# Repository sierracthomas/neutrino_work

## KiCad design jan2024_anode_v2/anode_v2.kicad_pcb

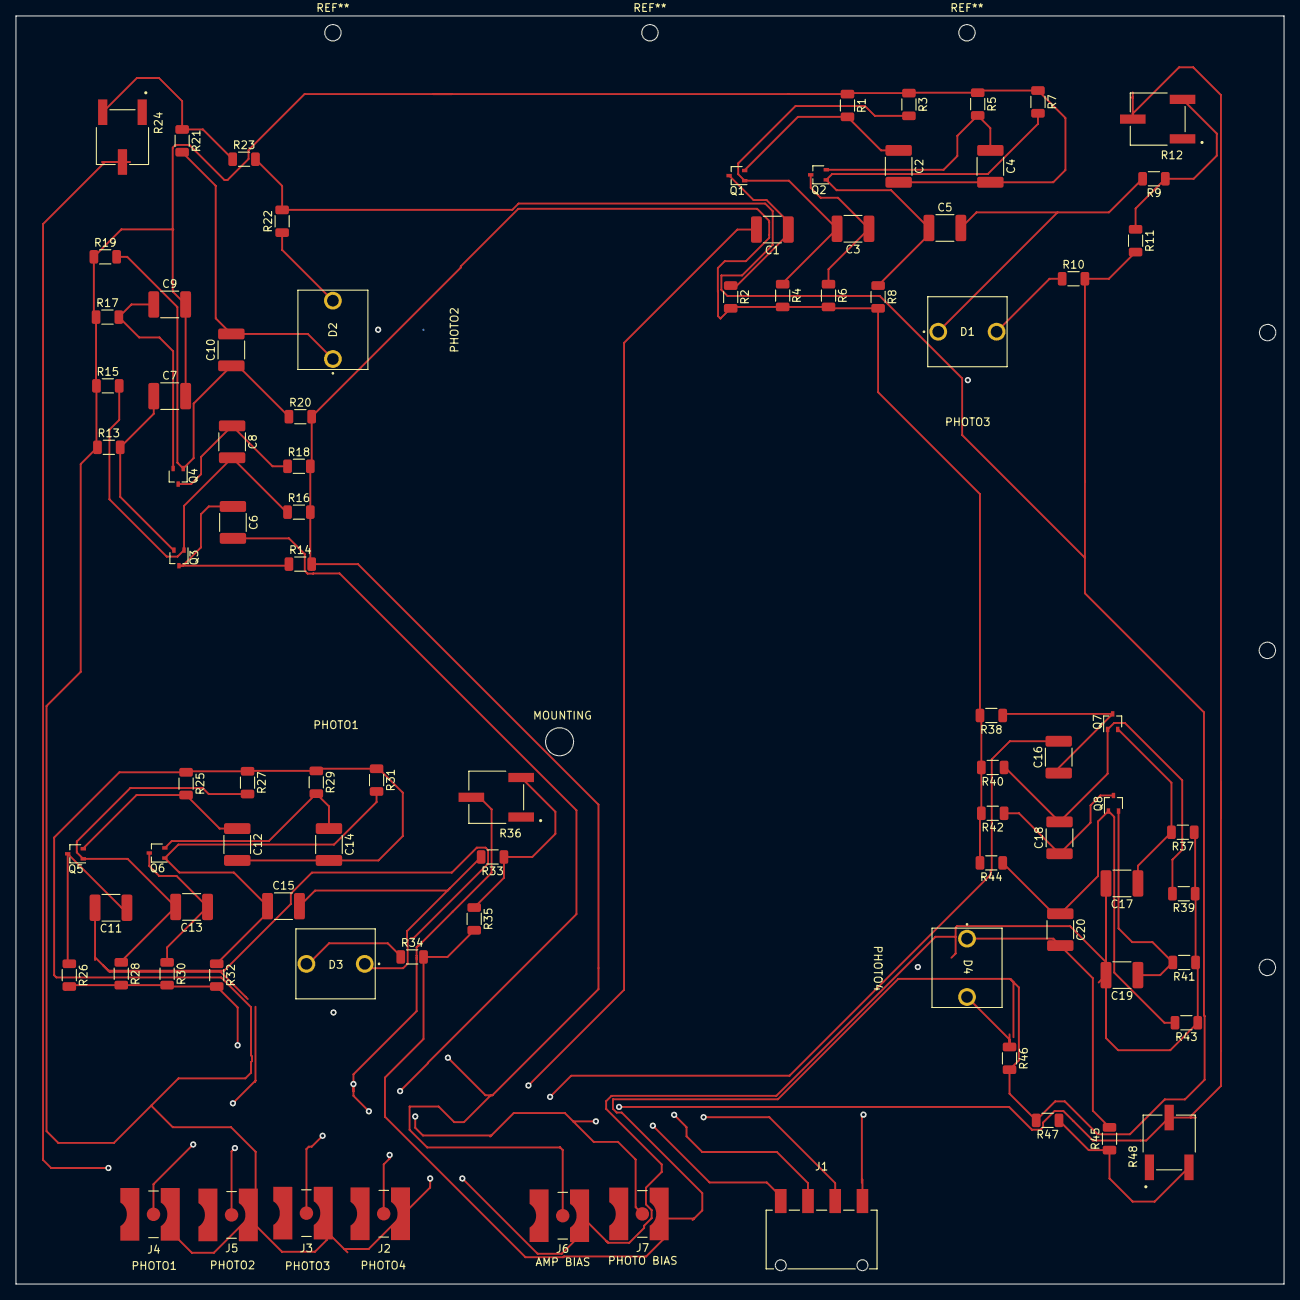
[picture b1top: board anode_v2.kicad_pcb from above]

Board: 4 copper layers, 163.0 x 163.0 mm, 88 parts (0 on the bottom side), 44 nets.

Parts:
C1, C2, C3, C4, C5, C6, C7, C8, C9, C10, C11, C12, C13, C14, C15, C16, C17, C18, C19, C20: C; C_1812_4532Metric
D1: PHOTO3; S13370-6075CN
D2: PHOTO2; S13370-6075CN
D3: PHOTO1; S13370-6075CN
D4: PHOTO4; S13370-6075CN
J1: 430450419; CONN4_2383942-4_TEC
J2: PHOTO4; LINX_CONMCX002-SMD
J3: PHOTO3; LINX_CONMCX002-SMD
J4: PHOTO1; LINX_CONMCX002-SMD
J5: PHOTO2; LINX_CONMCX002-SMD
J6: AMP BIAS; LINX_CONMCX002-SMD
J7: PHOTO BIAS; LINX_CONMCX002-SMD
MOUNTING: MountingHole_2.1mm
Q1, Q2, Q3, Q4, Q5, Q6, Q7, Q8: 2N3904; SOT-323_SC-70
R1, R2, R3, R4, R5, R6, R7, R8, R9, R10, R11, R13, R14, R15, R16, R17, R18, R19, R20, R21, R22, R23, R25, R26, R27, R28, R29, R30, R31, R32, R33, R34, R35, R37, R38, R39, R40, R41, R42, R43, R44, R45, R46, R47: R_US; R_1206_3216Metric
R12, R24, R36, R48: R_Variable_US; TRIM_3361P-1-104GLF

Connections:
/vuv sipm1/SIGNAL: C1.2, J3.1
/vuv sipm2/SIGNAL: C6.2, J5.1
/vuv sipm3/SIGNAL: C11.2, J4.1
/vuv sipm/SIGNAL: C16.2, J2.1
AMP_BIAS: J6.1, R2.2, R4.2, R6.2, R8.2, R14.2, R16.2, R18.2, R20.2, R26.2, R28.2, R30.2, R32.2, R38.2, R40.2, R42.2, R44.2
AMP_GND: C2.2, C4.2, C7.2, C9.2, C12.2, C14.2, C17.2, C19.2, J2.S1, J3.S1, J4.S1, J5.S1, J6.S1, R1.1, R3.1, R5.1, R7.1, R13.1, R15.1, R17.1, R19.1, R25.1, R27.1, R29.1, R31.1, R37.1, R39.1, R41.1, R43.1
BIAS: J7.1, R12.2, R24.2, R36.2, R48.2
GND: J7.S1, R10.2, R11.2, R22.2, R23.2, R34.2, R35.2, R46.2, R47.2
unnamed: C1.1, Q1.3 (C), R2.1
unnamed: C2.1, Q1.2 (E), R1.2
unnamed: C3.1, Q2.3 (C), R6.1
unnamed: C3.2, Q1.1 (B), R3.2, R4.1
unnamed: C5.1, Q2.1 (B), R7.2, R8.1
unnamed: C5.2, D1.1 (K), R9.2
unnamed: C6.1, Q3.3 (C), R14.1
unnamed: C7.1, Q3.2 (E), R13.2
unnamed: C8.1, Q4.3 (C), R18.1
unnamed: C8.2, Q3.1 (B), R15.2, R16.1
unnamed: C10.1, Q4.1 (B), R19.2, R20.1
unnamed: C10.2, D2.1 (K), R21.2
unnamed: C11.1, Q5.3 (C), R26.1
unnamed: C12.1, Q5.2 (E), R25.2
unnamed: C13.1, Q6.3 (C), R30.1
unnamed: C13.2, Q5.1 (B), R27.2, R28.1
unnamed: C15.1, Q6.1 (B), R31.2, R32.1
unnamed: C15.2, D3.1 (K), R33.2
unnamed: C17.1, Q7.2 (E), R37.2
unnamed: C18.1, Q8.3 (C), R42.1
unnamed: C20.1, Q8.1 (B), R43.2, R44.1
unnamed: C20.2, D4.1 (K), R45.2
unnamed: D1.2 (A), R10.1
unnamed: D2.2 (A), R22.1
unnamed: D3.2 (A), R34.1
unnamed: D4.2 (A), R46.1
unnamed: C4.1, Q2.2 (E), R5.2
unnamed: C9.1, Q4.2 (E), R17.2
unnamed: C14.1, Q6.2 (E), R29.2
unnamed: C19.1, Q8.2 (E), R41.2
unnamed: R9.1, R11.1, R12.3
unnamed: R21.1, R23.1, R24.3
unnamed: R33.1, R35.1, R36.3
unnamed: C16.1, Q7.3 (C), R38.1
unnamed: C18.2, Q7.1 (B), R39.2, R40.1
unnamed: R45.1, R47.1, R48.3

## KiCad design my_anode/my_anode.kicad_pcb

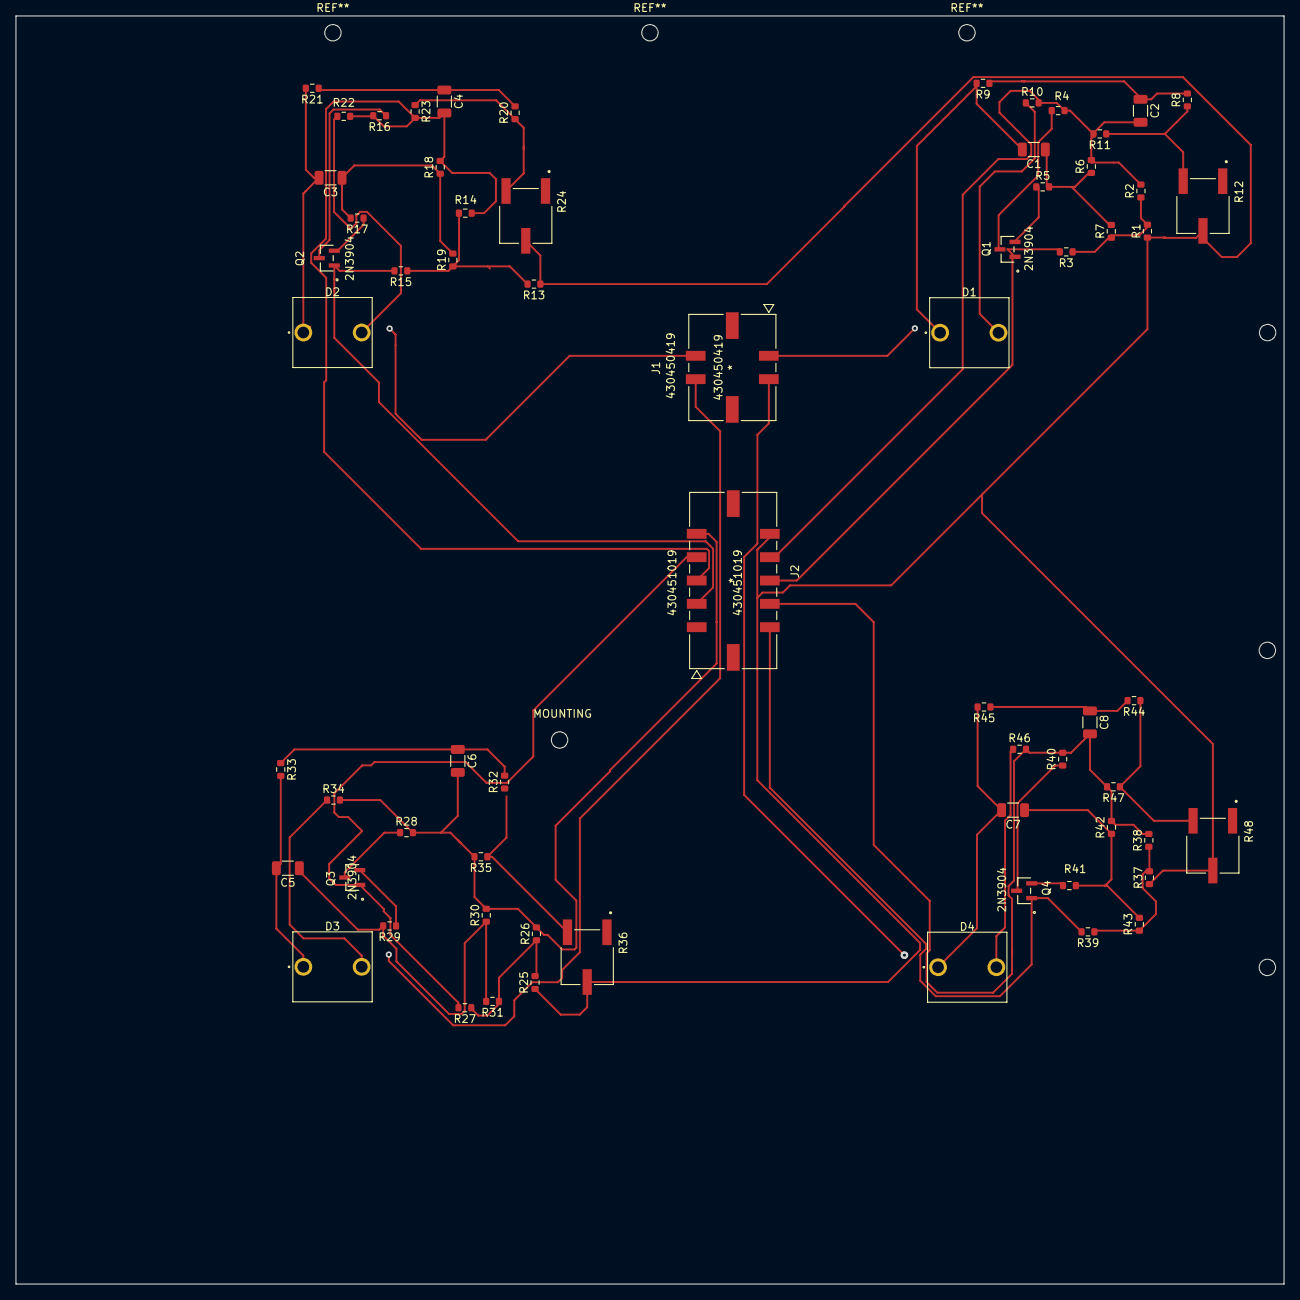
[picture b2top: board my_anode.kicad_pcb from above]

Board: 2 copper layers, 163.0 x 163.0 mm, 67 parts (0 on the bottom side), 41 nets.

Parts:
C1, C2, C3, C4, C5, C6, C7, C8: C; C_1206_3216Metric
D1, D2, D3, D4: D_Photo; S13370-6075CN
J1: 430450419
J2: 430451019
MOUNTING: MountingHole_2.1mm
Q1, Q2, Q3, Q4: 2N3904; BC846BLT3G
R1, R2, R3, R4, R5, R6, R7, R8, R9, R10, R11, R13, R14, R15, R16, R17, R18, R19, R20, R21, R22, R23, R25, R26, R27, R28, R29, R30, R31, R32, R33, R34, R35, R37, R38, R39, R40, R41, R42, R43, R44, R45, R46, R47: R_US; R_0603_1608Metric
R12, R24, R36, R48: R_Variable_US; TRIM_3361P-1-104GLF

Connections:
/B1: J2.10, R1.1, R12.2, R13.1, R24.2, R25.1, R36.2, R37.1, R48.2
/G1: C4.2, J2.3, R14.2, R16.2, R18.2, R22.2, R23.2
/G2: C6.2, J2.5, R26.2, R28.2, R30.2, R34.2, R35.2
/G3: C8.2, J2.7, R38.2, R40.2, R42.2, R46.2, R47.2
/G4: C2.2, J2.9, R2.2, R4.2, R6.2, R10.2, R11.2
/S1: J2.2, Q2.1 (E), R15.2
/S2: J2.4, Q3.1 (E), R27.2
/S3: J2.6, Q4.1 (E), R39.2
/S4: J2.8, Q1.1 (E), R3.2
unnamed: C1.1, R5.2, R6.1, R7.2
unnamed: C1.2, D1.1 (K), R9.2
unnamed: C2.1, R8.2, R9.1
unnamed: C3.1, R17.2, R18.1, R19.2
unnamed: C3.2, D2.1 (K), R21.2
unnamed: C4.1, R20.2, R21.1
unnamed: C5.1, R29.2, R30.1, R31.2
unnamed: C5.2, D3.1 (K), R33.2
unnamed: C6.1, R32.2, R33.1
unnamed: C7.1, R41.2, R42.1, R43.2
unnamed: C7.2, D4.1 (K), R45.2
unnamed: C8.1, R44.2, R45.1
unnamed: D1.2 (A), R10.1
unnamed: D2.2 (A), R22.1
unnamed: D3.2 (A), R34.1
unnamed: D4.2 (A), R46.1
unnamed: Q1.2 (B), R5.1
unnamed: Q1.3 (C), R4.1
unnamed: Q2.2 (B), R17.1
unnamed: Q2.3 (C), R16.1
unnamed: Q3.2 (B), R29.1
unnamed: Q3.3 (C), R28.1
unnamed: Q4.2 (B), R41.1
unnamed: Q4.3 (C), R40.1
unnamed: R1.2, R2.1, R3.1, R7.1
unnamed: R8.1, R11.1, R12.3
unnamed: R13.2, R14.1, R15.1, R19.1
unnamed: R20.1, R23.1, R24.3
unnamed: R25.2, R26.1, R27.1, R31.1
unnamed: R32.1, R35.1, R36.3
unnamed: R37.2, R38.1, R39.1, R43.1
unnamed: R44.1, R47.1, R48.3

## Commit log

2022-12-13 initial files and structure
2022-12-13 add fornax data
2022-12-13 Plots with binning
2022-12-14 add binned interaction plots
2022-12-14 add model data and updated scripts
2022-12-15 plot final touches
2023-01-05 Add more documentation
2023-01-05 add README
2023-01-05 README updates
2023-01-05 clear some chaos
2023-01-31 Update fluence to work with 2d plots
2023-02-03 Add anode project
2023-02-17 set times to be the same, fix `vmin` and `vmax`
2023-02-17 Update anode work with mounting holes
2023-02-26 Add quarter-anode board
2023-03-17 Semi-final board version without voltage divider
2023-03-24 add photodiode dark current data
2023-05-01 Add prelim compton scatter example w/ geant script
2023-05-01 V1 with voltage divider
2023-05-02 Trial w/ 20 hits - graph coincident compton scatters
2023-05-04 Add functions to plot integrated electron energy
2023-05-10 Add anode prior to copying
2023-05-15 Add spectrum energy level runs
2023-05-17 New script gets process files
2023-05-17 Subtract all combinations of tracks in pd.dataframe
2023-05-17 Get unique tracks for event 0 that are > 10mm away
2023-05-17 Ignore performance warnings
2023-05-18 Add length vs energy for blips/blobs
2023-05-21 Add new code for blips/blobs in liquid argon detector
2023-05-22 Add histograms for blobs/blips
2023-06-12 Add cross sections for 40Ar calculated by TALYS
2023-06-13 Add cross section of Ar de-ex gammas
2023-06-15 Add cross-sections by level
2023-10-05 Add independent study folder with oscillations assignment
2023-10-20 Progress + derivation of the hamiltonian w/ perturbation
2023-10-20 Add reference and clarify epsilon definition
2024-01-22 Anode version with double-phase transistor amplifier

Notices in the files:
parts and their libraries:
Copyright 2016 Accelerated Designs. All rights reserved.
Copyright 2021 Accelerated Designs. All rights reserved.
